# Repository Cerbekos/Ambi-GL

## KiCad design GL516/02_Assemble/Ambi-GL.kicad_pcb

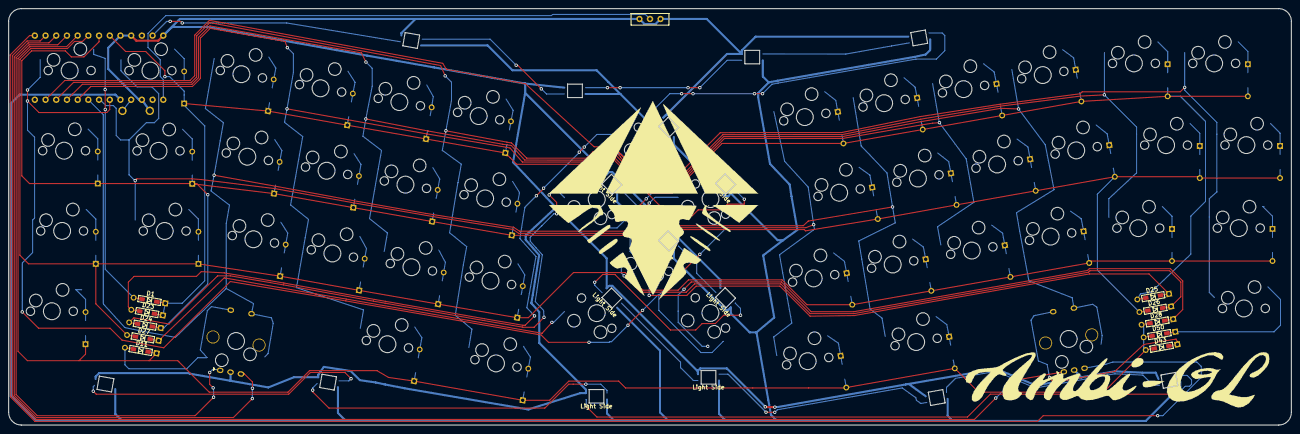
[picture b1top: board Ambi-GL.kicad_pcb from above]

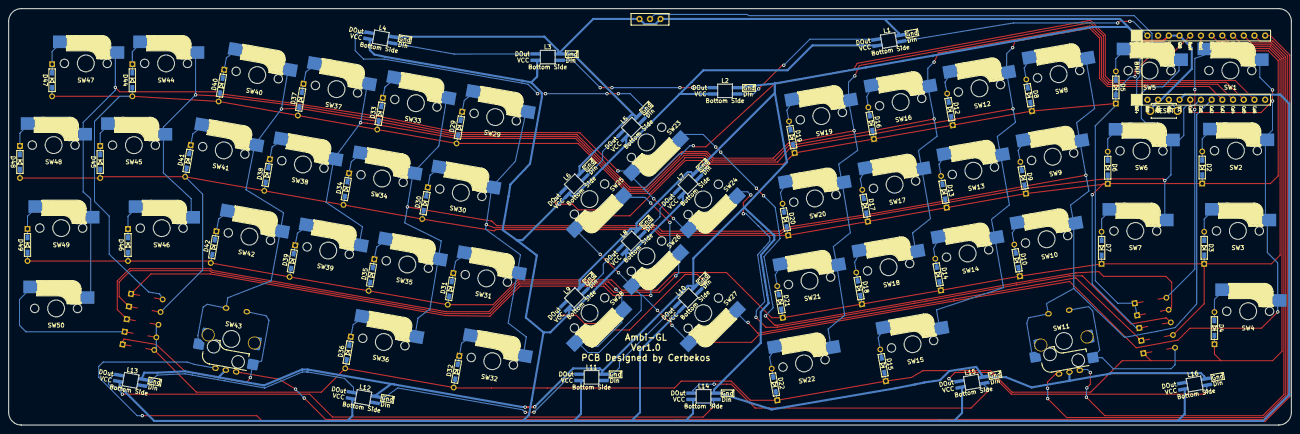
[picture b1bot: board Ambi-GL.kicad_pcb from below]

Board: 2 copper layers, 304.3 x 98.8 mm, 119 parts (11 on the bottom side), 85 nets.

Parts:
D1, D2, D3, D4, D5, D6, D7, D8, D9, D10, D11, D12, D13, D14, D15, D16, D17, D18, D19, D20, D21, D22, D23, D24, D25, D26, D27, D28, D29, D30, D31, D32, D33, D34, D35, D36, D37, D38, D39, D40, D41, D42, D43, D44, D45, D46, D47, D48, D49, D50: D; Diode_TH_SMD
J1: Conn_01x02; Battery_XH2.5_GL_PCB
L1, L2, L3, L4, L5, L6, L7, L8, L9, L10, L11, L12, L13, L14, L15, L16: SK6812MINI; LED_SK6812MINI-E_BL
SW1, SW5, SW6, SW7, SW8, SW9, SW10, SW12, SW13, SW14, SW16, SW17, SW18, SW19, SW20, SW21, SW22, SW23, SW24, SW25, SW26, SW27, SW28, SW29, SW30, SW31, SW32, SW33, SW34, SW35, SW37, SW38, SW39, SW40, SW41, SW42, SW44, SW45, SW46, SW47, SW48: SW_PUSH; CherryMX_Hotswap_1.0u
SW2, SW4, SW50: SW_PUSH; CherryMX_Hotswap_1.25u
SW3, SW49: SW_PUSH; CherryMX_Hotswap_1.5u
SW11, SW43: Rotary_Encoder_Switch; SW_Cherry_MX_1.00u_Kailh_EC12_my
SW15, SW36: SW_PUSH; CherryMX_Hotswap_1.75u
SW51: SW_PUSH; ResetSW
U1: BLEMicroPro; Micon_BMP_GL

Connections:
A1: SW11.A, U1.9
B1: SW11.B, U1.10
Bat+: J1.1, U1.25
C1: SW43.A, U1.11
Col0: SW1.1, SW2.1, SW3.1, SW4.1, SW25.1, SW26.1, SW27.1, SW28.1, U1.20
Col1: SW5.1, SW6.1, SW7.1, SW29.1, SW30.1, SW31.1, SW32.1, U1.19
Col2: SW8.1, SW9.1, SW10.1, SW11.S2, SW33.1, SW34.1, SW35.1, SW36.1, U1.18
Col3: SW12.1, SW13.1, SW14.1, SW15.1, SW37.1, SW38.1, SW39.1, U1.17
Col4: SW16.1, SW17.1, SW18.1, SW40.1, SW41.1, SW42.1, SW43.S2, U1.16
Col5: SW19.1, SW20.1, SW21.1, SW22.1, SW44.1, SW45.1, SW46.1, U1.15
Col6: SW23.1, SW24.1, SW47.1, SW48.1, SW49.1, SW50.1, U1.14
D1: SW43.B, U1.12
GND: J1.2, L1.2, L2.2, L3.2, L4.2, L5.2, L6.2, L7.2, L8.2, L9.2, L10.2, L11.2, L12.2, L13.2, L14.2, L15.2, L16.2, SW11.C, SW43.C, SW51.2, U1.3, U1.4, U1.23, U1.26
LED: L1.3, U1.1
unnamed: D1.2, SW1.2
unnamed: D2.2, SW2.2
unnamed: D3.2, SW3.2
unnamed: D4.2, SW4.2
unnamed: D5.2, SW5.2
unnamed: D6.2, SW6.2
unnamed: D7.2, SW7.2
unnamed: D8.2, SW8.2
unnamed: D9.2, SW9.2
unnamed: D10.2, SW10.2
unnamed: D11.2, SW11.S1
unnamed: D12.2, SW12.2
unnamed: D13.2, SW13.2
unnamed: D14.2, SW14.2
unnamed: D15.2, SW15.2
unnamed: D16.2, SW16.2
unnamed: D17.2, SW17.2
unnamed: D18.2, SW18.2
unnamed: D19.2, SW19.2
unnamed: D20.2, SW20.2
unnamed: D21.2, SW21.2
unnamed: D22.2, SW22.2
unnamed: D23.2, SW23.2
unnamed: D24.2, SW24.2
unnamed: D25.1, SW25.2
unnamed: D26.1, SW26.2
unnamed: D27.1, SW27.2
unnamed: D28.1, SW28.2
unnamed: D29.1, SW29.2
unnamed: D30.1, SW30.2
unnamed: D31.1, SW31.2
unnamed: D32.1, SW32.2
unnamed: D33.1, SW33.2
unnamed: D34.1, SW34.2
unnamed: D35.1, SW35.2
unnamed: D36.1, SW36.2
unnamed: D37.1, SW37.2
unnamed: D38.1, SW38.2
unnamed: D39.1, SW39.2
unnamed: D40.1, SW40.2
unnamed: D41.1, SW41.2
unnamed: D42.1, SW42.2
unnamed: D43.1, SW43.S1
unnamed: D44.1, SW44.2
unnamed: D45.1, SW45.2
unnamed: D46.1, SW46.2
unnamed: D47.1, SW47.2
unnamed: D48.1, SW48.2
unnamed: D49.1, SW49.2
unnamed: D50.1, SW50.2
unnamed: L1.1, L2.3
unnamed: L2.1, L3.3
unnamed: L3.1, L4.3
unnamed: L4.1, L5.3
unnamed: L5.1, L6.3
unnamed: L6.1, L7.3
unnamed: L7.1, L8.3
unnamed: L8.1, L9.3
unnamed: L10.1, L11.3
unnamed: L9.1, L10.3
unnamed: L11.1, L12.3
unnamed: L12.1, L13.3
unnamed: L13.1, L14.3
unnamed: L14.1, L15.3
unnamed: L15.1, L16.3
Reset: SW51.1, U1.22
Row0: D1.1, D5.1, D8.1, D12.1, D16.1, D19.1, D23.1, D25.2, D29.2, D33.2, D37.2, D40.2, D44.2, D47.2, U1.5
Row1: D2.1, D6.1, D9.1, D13.1, D17.1, D20.1, D24.1, D26.2, D30.2, D34.2, D38.2, D41.2, D45.2, D48.2, U1.6
Row2: D3.1, D7.1, D10.1, D14.1, D18.1, D21.1, D27.2, D31.2, D35.2, D39.2, D42.2, D46.2, D49.2, U1.7
Row3: D4.1, D11.1, D15.1, D22.1, D28.2, D32.2, D36.2, D43.2, D50.2, U1.8
VCC: L1.4, L2.4, L3.4, L4.4, L5.4, L6.4, L7.4, L8.4, L9.4, L10.4, L11.4, L12.4, L13.4, L14.4, L15.4, L16.4, U1.21

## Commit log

2022-01-03 add new file
